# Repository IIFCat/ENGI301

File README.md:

# Repository for ENGI301 course work

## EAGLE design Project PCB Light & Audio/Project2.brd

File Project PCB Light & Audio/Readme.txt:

Project PCB for Audio & Light

Following the previous project, I practiced designing PCB by making this board which contains one USB jack for audio outputs and 3 RGB LEDs. This board is compatible with PocketBeagle.

Some components are adapted from Beaglebone Black Wireless.

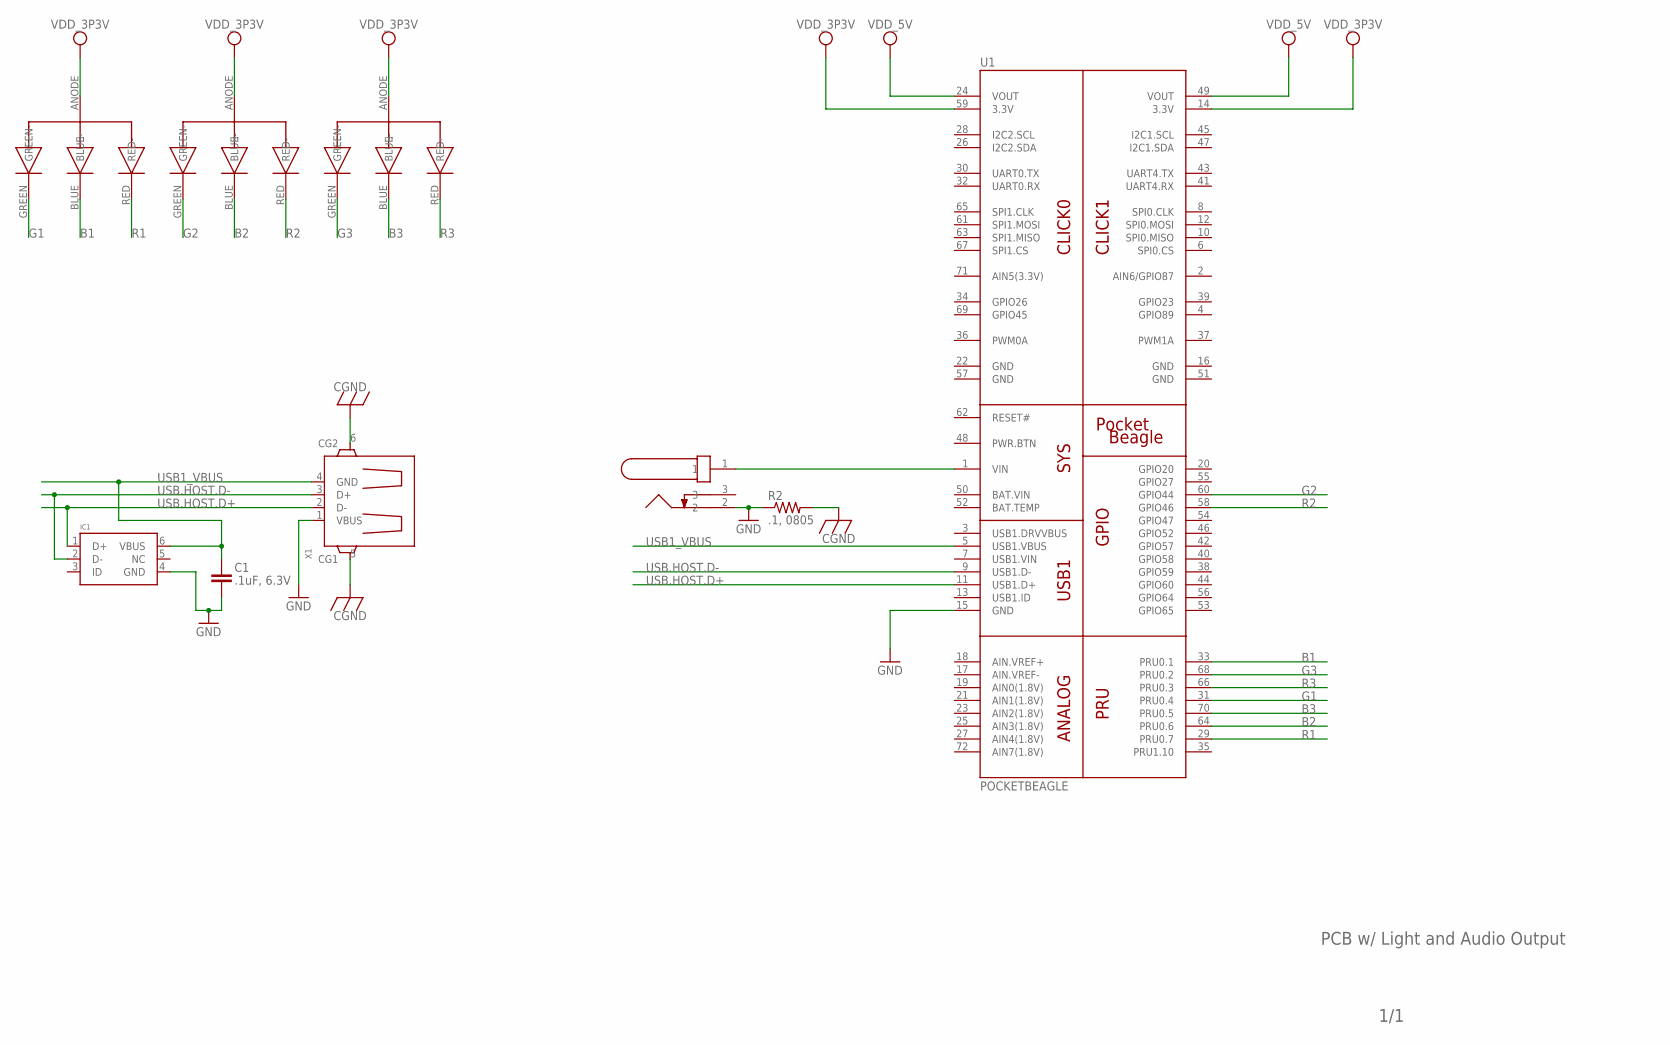
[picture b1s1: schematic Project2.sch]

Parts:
C1: .1uF, 6.3V; C0402
IC1: DRY; SON-6(TI)-DRY
R2: .1, 0805; RCL_R0805
U1: POCKETBEAGLE
U$1, U$3, U$4: RGBLED-LX0404; SML-LX0404SIUPGUSB
U$2: PJ-202; PJ-202A
X1: USB_HOST

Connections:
B1: U1.33 (PRU0.1), U$1.BLUE (BLUE-)
B2: U1.64 (PRU0.6), U$3.BLUE (BLUE-)
B3: U1.70 (PRU0.5), U$4.BLUE (BLUE-)
BAT.VIN: U1.50 (BAT.VIN)
CGND: R2.2, X1.5 (CG1), X1.6 (CG2)
G1: U1.31 (PRU0.4), U$1.GREEN (GREEN-)
G2: U1.60 (GPIO44), U$3.GREEN (GREEN-)
G3: U1.68 (PRU0.2), U$4.GREEN (GREEN-)
GND: C1.2, IC1.4 (GND), R2.1, U1.15 (GND), U1.16 (GND), U1.22 (GND), U1.51 (GND), U1.57 (GND), U$2.2, X1.1 (VBUS)
unnamed: U1.1 (VIN), U$2.1
R1: U1.29 (PRU0.7), U$1.RED (RED-)
R2: U1.58 (GPIO46), U$3.RED (RED-)
R3: U1.66 (PRU0.3), U$4.RED (RED-)
USB1_VBUS: C1.1, IC1.6 (VBUS), U1.5 (USB1.VBUS), X1.4 (GND)
USB.HOST.D+: IC1.1 (D+), U1.11 (USB1.D+), X1.2 (D-)
USB.HOST.D-: IC1.2 (D-), U1.9 (USB1.D-), X1.3 (D+)
VDD_3P3V: U1.14 (3.3V), U1.59 (3.3V), U$1.ANODE (+), U$3.ANODE (+), U$4.ANODE (+)
VDD_5V: U1.24 (VOUT), U1.49 (VOUT)

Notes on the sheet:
PCB w/ Light and Audio Output
1/1

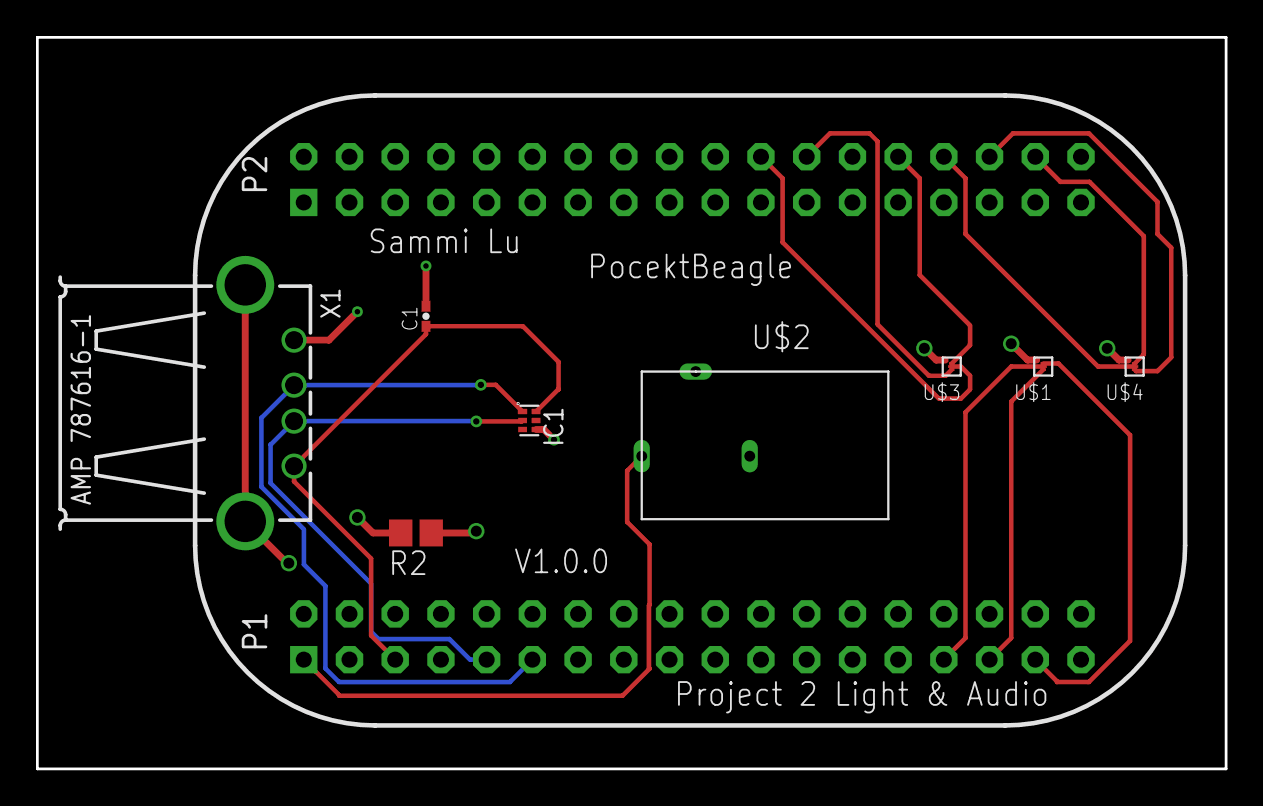
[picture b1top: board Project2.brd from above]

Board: 4 copper layers, 66.0 x 40.6 mm, 9 parts (0 on the bottom side), 17 nets.

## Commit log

2018-09-10 no message
2018-09-26 /Users/YadaHomra/Downloads/simple_calc (2).py /Users/YadaHomra/Downloads/blink_USR3.py
2018-09-26 Create simple_calc
2018-09-26 /Users/YadaHomra/ENGI301/blink_USR3.py
2018-09-26 /Users/YadaHomra/ENGI301/blink_USR3.py /Users/YadaHomra/ENGI301/simple_calc.py
2018-09-26 I really don't want to mess up this again.
2018-10-12 This is for project Lighted Castle. Updated by Oct 12th, 2018.
2018-11-05 Update after project is almost complete.
2018-11-05 RTF file not readable
2018-11-20 Project 2 for ENGI 301
2018-12-10 Project 2 Updated by 12/10/2018
